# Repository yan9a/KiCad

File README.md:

# KiCad
KiCad Getting Started in Myanmar

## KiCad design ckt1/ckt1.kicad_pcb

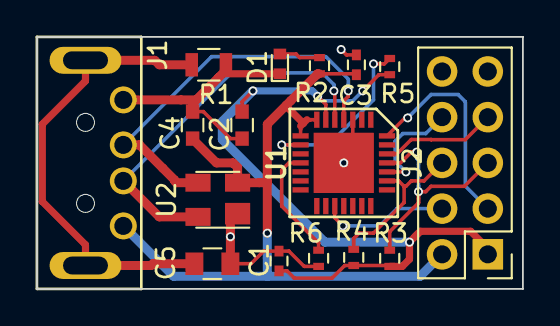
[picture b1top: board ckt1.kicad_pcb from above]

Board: 2 copper layers, 27.0 x 14.0 mm, 16 parts (0 on the bottom side), 15 nets.

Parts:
C1, C3: 0.1uF; C_0402
C2, C4: 4.7uF; C_0603
C5: 100pF; C_0805
D1: LED; LED_0402
J1: USB_A; USB_A_Plug
J2: CONN_02X05; Pin_Header_Straight_2x05_Pitch2.54mm
R1: 1M; R_0805
R2: 2k2; R_0402
R3, R4, R6: 10k; R_0402
R5: 1k; R_0402
U1: CP2102N; QFN28
U2: SP0503BAHTG; SOT-143

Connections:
/CTS: J2.6, R4.2, U1.23
/D+: J1.3, U1.4, U2.3
/D-: J1.2, U1.5, U2.4
/DTR: J2.3, U1.28
/RS485: J2.4, U1.17
/RTS: J2.8, U1.24
/RXD: J2.5, R3.2, U1.25
/TXD: J2.7, U1.26
GND: C1.2, C2.2, C3.2, C4.2, C5.1, D1.1, J1.4, J2.9, J2.10, R1.1, R6.1, U1.3, U1.29, U2.1
GNDPWR: C5.2, J1.5, R1.2
unnamed: D1.2, R2.2
unnamed: R5.2, U1.9
unnamed: R6.2, U1.11
VCC: C3.1, C4.1, J1.1, J2.2, R2.1, U1.7, U1.8, U2.2
VDD: C1.1, C2.1, J2.1, R3.1, R4.1, R5.1, U1.6

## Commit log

2017-07-29 Added kicadmm pdf book
